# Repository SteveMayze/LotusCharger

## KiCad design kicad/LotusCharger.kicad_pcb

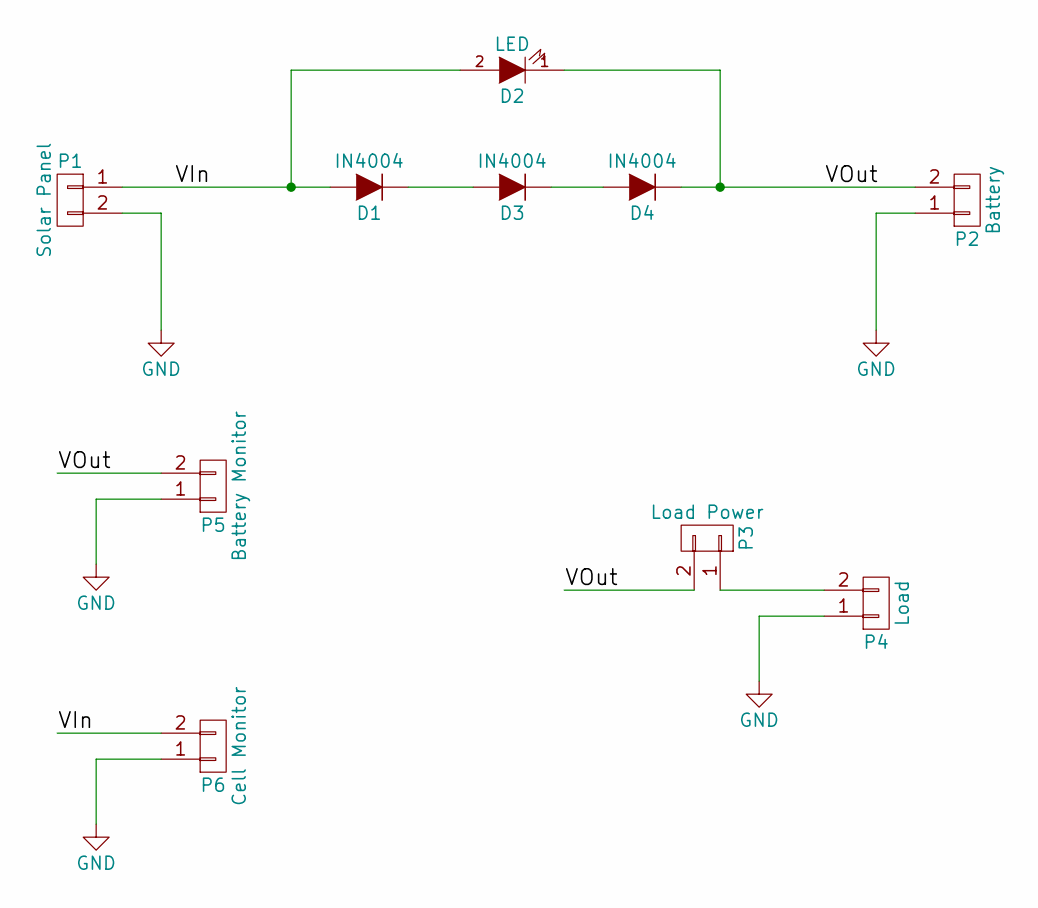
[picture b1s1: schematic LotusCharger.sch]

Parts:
D1, D3, D4: IN4004; D_DO-41_SOD81_P10.16mm_Horizontal
D2: LED; LED_D5.0mm
P1: Solar Panel; PCB_Screw_Terminal_Block_5.08mm_x_2
P2: Battery; PCB_Screw_Terminal_Block_5.08mm_x_2
P3: Load Power; PCB_Screw_Terminal_Block_5.08mm_x_2
P4: Load; PCB_Screw_Terminal_Block_5.08mm_x_2
P5: Battery Monitor; TerminalBlock_Pheonix_MPT-2.54mm_2pol
P6: Cell Monitor; TerminalBlock_Pheonix_MPT-2.54mm_2pol

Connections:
/VIn: D1.2 (A), D2.2 (A), P1.1, P6.2
/VOut: D2.1 (K), D4.1 (K), P2.2, P3.2, P5.2
GND: P1.2, P2.1, P4.1, P5.1, P6.1
unnamed: D1.1 (K), D3.2 (A)
unnamed: D3.1 (K), D4.2 (A)
unnamed: P3.1, P4.2

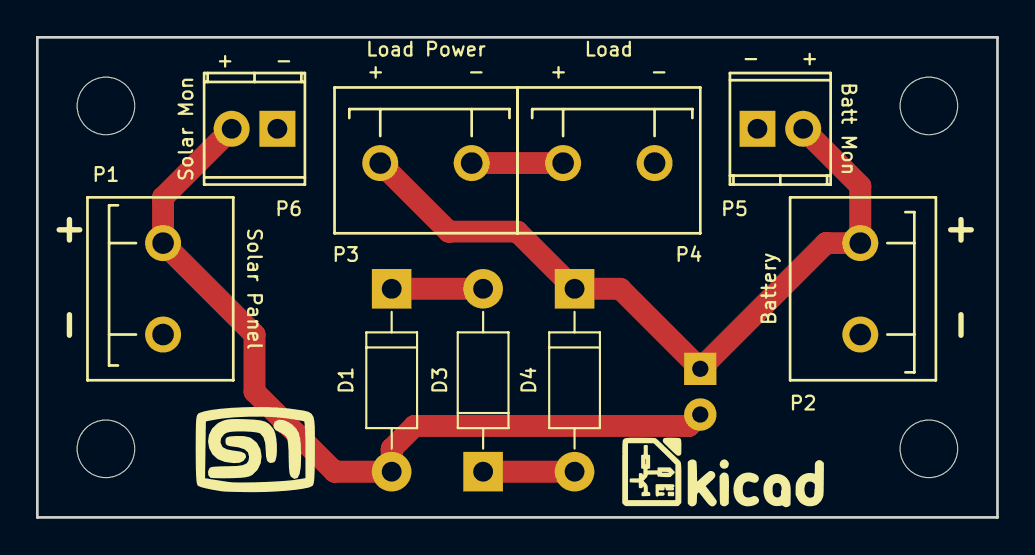
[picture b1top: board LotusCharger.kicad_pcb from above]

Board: 2 copper layers, 53.3 x 26.7 mm, 11 parts (1 on the bottom side), 6 nets.

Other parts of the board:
LGO***: LOGO; KiCad-Logo

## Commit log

2017-09-17 Directory shuffel
2017-09-17 Layout finished and sending to Fab.
